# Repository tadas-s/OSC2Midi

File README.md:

# OSC2Midi

ESP8266 based OSC <-> Midi wireless bridge.

It is mostly meant to be used with [TouchOSC][1] but it will work with
any [OSC message source][2].

## Library dependencies

Project uses:
  * https://github.com/FortySevenEffects/arduino_midi_library/
  * https://github.com/CNMAT/OSC

## Hardware

Based on a generic ESP8266-12f board and the following guides to hook
up ESP8266 and do MIDI i/o:

  * [MIDI Input][4]
  * [MIDI Output][3]

Midi I/O uses [SoftwareSerial][5] mostly to allow debug logging via
primary serial port.

## Schematic

Note! Do checkout the KiCad project instead. Image below is for quick preview only.

## Flashing firmware

To flash the firmware I'm using FTDI cable with [flash+reset circuit][8].

## Hardware ideas / roadmap / TODO

  * Find a reasonable enclosure and adapt layout to it.
  * [MCP73833][7] based battery charging circuit + microusb input for power.
  * Maaaaybe i2c screen.

## OSC message formats

All messages are expected to have payload of 1 or 2 floats with range
from 0 to 127.

### /midi/cc/{cc} + 1 float

Will send control change message for `{cc}` number.

### /midi/cc/{ccA}/{ccB}/.../{index} + 1 float

Will send control change message for CC specified by `{index}`. For
example:

  * /midi/cc/10/12/15/1 -> CC to 10
  * /midi/cc/10/12/15/3 -> CC to 15

This is meant to be used with TouchOSC groups of faders. For example,
my [MicroKORG][6] preset includes a fader group of 4 to control
amp ADSR: `/midi/cc/73/75/70/72`

### /midi/cc/{ccA}/{ccB} + 2 floats

This sends two control change messages to `{ccA}` and `{ccB}`. This is
meant to be used with TouchOSC XY pads.

## Current prototype

Rather crude build, but it works:

## Hello people of the future

So it seems GitHub is about to take a snapshot of active open source repositories
and put it into cold storage that should last 1000 years. Hence this section:
a change for the sake of it. Exact criteria is not clear, but hope this
repository makes it to the archive.

[1]: http://hexler.net/software/touchosc
[2]: https://en.wikipedia.org/wiki/Open_Sound_Control
[3]: https://www.arduino.cc/en/Tutorial/Midi
[4]: http://libremusicproduction.com/tutorials/arduino-and-midi-in
[5]: https://www.arduino.cc/en/Reference/SoftwareSerial
[6]: http://www.korg.com/us/products/synthesizers/microkorg/
[7]: https://www.microchip.com/wwwproducts/en/en027785
[8]: https://github.com/tadas-s/esp8266-autoreset

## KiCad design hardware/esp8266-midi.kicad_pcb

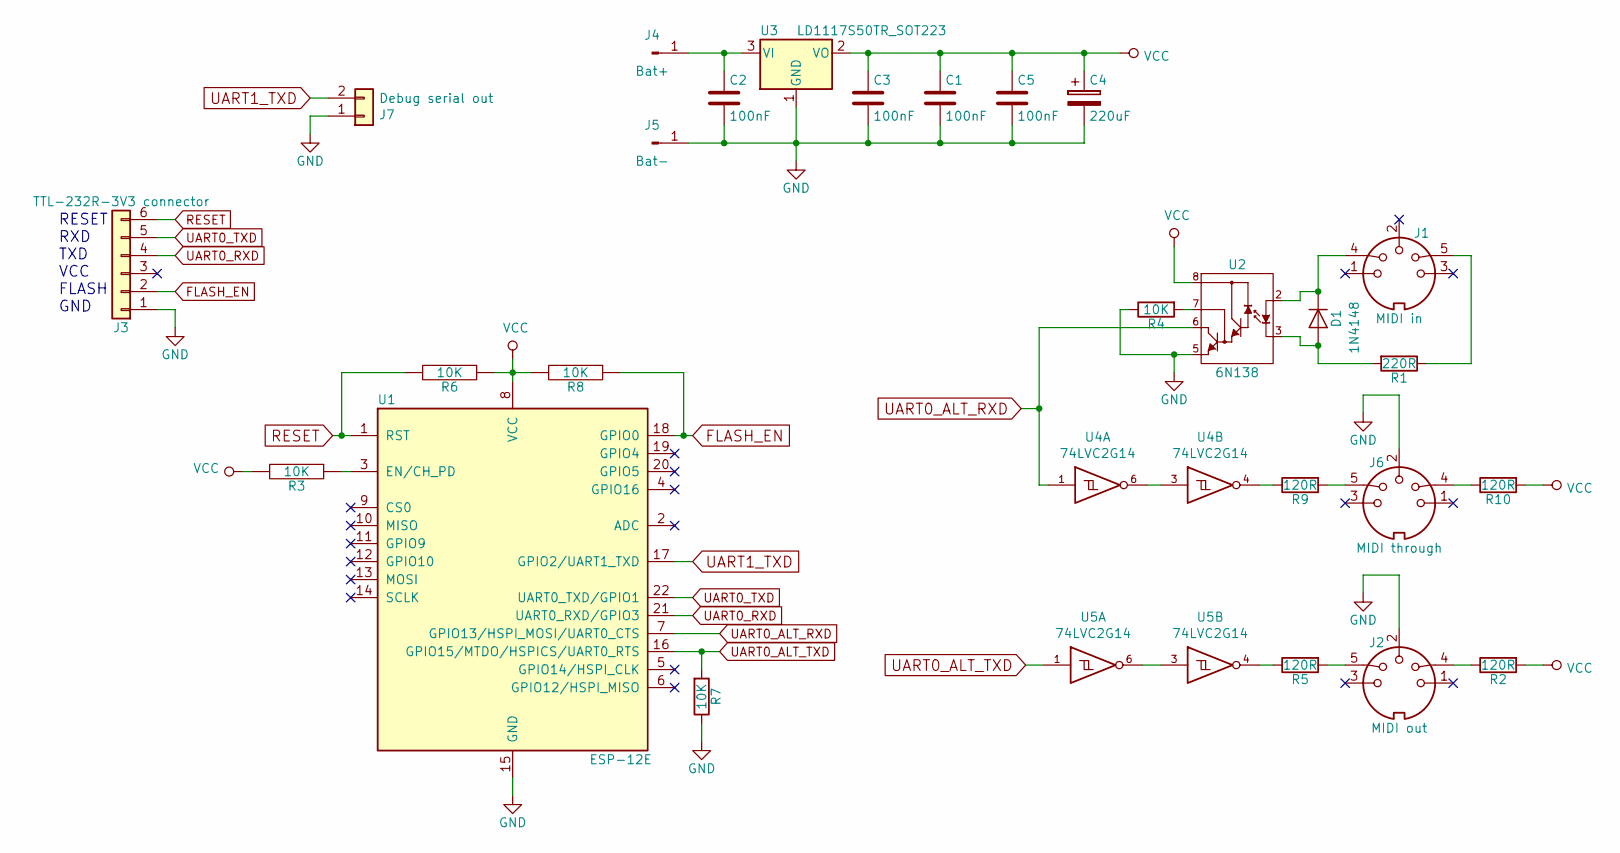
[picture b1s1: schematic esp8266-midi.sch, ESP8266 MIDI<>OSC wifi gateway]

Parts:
C1, C2, C3, C5: 100nF; C_0805_HandSoldering
C4: 220uF; CP_Elec_6.3x5.8
D1: 1N4148; D_SOD-323_HandSoldering
J1: MIDI in; SDS-50J
J2: MIDI out; SDS-50J
J3: TTL-232R-3V3 connector; Pin_Header_Straight_1x06_Pitch2.54mm
J4: Bat+; SolderWirePad_single_0-8mmDrill
J5: Bat-; SolderWirePad_single_0-8mmDrill
J6: MIDI through; SDS-50J
J7: Debug serial out; Pin_Header_Straight_1x02_Pitch2.54mm
R1: 220R; R_0805_HandSoldering
R2, R5, R9, R10: 120R; R_0805_HandSoldering
R3, R4, R6, R7, R8: 10K; R_0805_HandSoldering
U1: ESP-12E
U2: 6N138; DIP-8_W7.62mm_SMDSocket_SmallPads
U3: LD1117S50TR_SOT223; SOT-223
U4, U5: 74LVC2G14; SOT-23-6_Handsoldering

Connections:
FLASH_EN: J3.2, R8.1, U1.18 (GPIO0)
GND: C1.2, C2.2, C3.2, C4.2, C5.2, J2.2, J3.1, J5.1, J6.2, J7.1, R4.1, R7.1, U1.15 (GND), U2.5 (GND), U3.1 (GND), U4.2 (GND), U5.2 (GND)
unnamed: C2.1, J4.1, U3.3 (VI)
unnamed: D1.1 (K), J1.4, U2.2 (A)
unnamed: D1.2 (A), R1.2, U2.3 (K)
unnamed: J1.5, R1.1
unnamed: J2.4, R2.1
unnamed: J2.5, R5.2
unnamed: J6.4, R10.1
unnamed: J6.5, R9.2
unnamed: R3.1, U1.3 (EN/CH_PD)
unnamed: R4.2, U2.7 (Vb)
unnamed: R5.1, U5.4
unnamed: R9.1, U4.4
unnamed: U4.3, U4.6
unnamed: U5.3, U5.6
RESET: J3.6, R6.2, U1.1 (RST)
UART0_ALT_RXD: U1.7 (GPIO13/HSPI_MOSI/UART0_CTS), U2.6 (Vo), U4.1
UART0_ALT_TXD: R7.2, U1.16 (GPIO15/MTDO/HSPICS/UART0_RTS), U5.1
UART0_RXD: J3.4, U1.21 (UART0_RXD/GPIO3)
UART0_TXD: J3.5, U1.22 (UART0_TXD/GPIO1)
UART1_TXD: J7.2, U1.17 (GPIO2/UART1_TXD)
VCC: C1.1, C3.1, C4.1, C5.1, R2.2, R3.2, R6.1, R8.2, R10.2, U1.8 (VCC), U2.8 (Vcc), U3.2 (VO), U4.5 (VCC), U5.5 (VCC)

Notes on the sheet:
RESET RXD TXD VCC FLASH GND

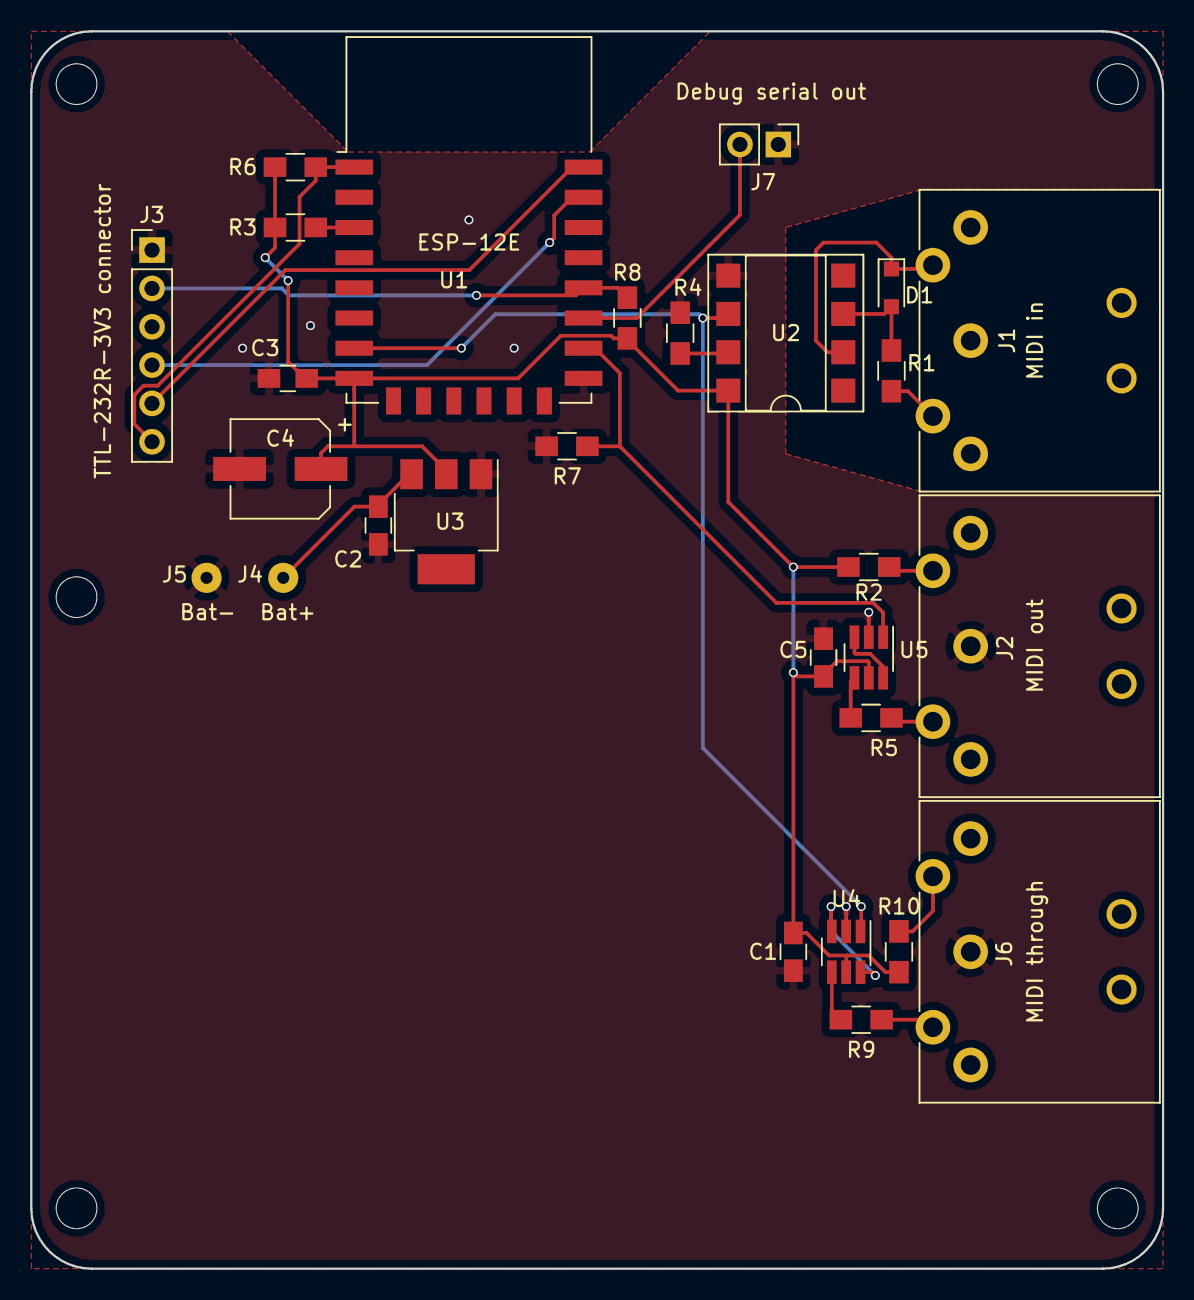
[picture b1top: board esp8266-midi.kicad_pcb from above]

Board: 2 copper layers, 75.0 x 82.0 mm, 28 parts (0 on the bottom side), 23 nets.

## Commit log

2016-08-15 Quick and dirty OSC<->Midi bridge mockup
2016-08-15 Add a note about library dependencies
2018-03-08 Misc: note about software serial pins
2018-03-08 Update README.md
    Mixed up links to midi in and out schematics
2018-03-10 Initial rev of schematic and PCB, WIP
2018-03-10 Misc README.md updates
2018-03-13 Misc README.md notes
2018-04-03 Misc: tweaks trying to figure out Android's "authentication error"
    Maybe it's the early start, maybe something else.. Or maybe persisted
    credentials from before?
2018-04-04 Update schematic: now uses ESP-12E footprint from standard KiCad lib
    + Misc silly fixes.
2018-04-04 Updated PCB using correct ESP-12E footprint
2018-04-08 Soft serial requires pins to be configured before starting
    Also, due to the way hardware works it input must always be pulled
    high.
2018-04-08 Don't use the same port to send controls over back to the controller
2018-04-08 Schematic change: do not pull up opto-isolator output + change output resistor loop values
    1. Pull up can be done by the micro itself.
    2. 220 ohm examples are taken from Midi spec when voltage is 5v. To match the
    the same current when using 3.3v micro resistors were reduced to 120ohm.
2018-04-08 Hopefully fixed layout now
2018-04-09 Before resizing the board a bit
2018-04-09 Small resize of the board + relocating some stuff + some rounded ground zone corners
2018-04-11 Notes added by 'git notes add'
2018-04-24 Misc cleanup: remove some TODOs/notes. Schematic is verified / works.
2018-04-24 Not sure why but KiCad decided to update project file a bit...
2018-04-24 Add schematic preview to README.md
2018-04-24 Slightly better debug info: display midi cc+values instead of just message only
2018-05-29 Misc: re-freshed schematic preview
2018-06-02 Misc: change "candidate" enclosure to CRDCGG003 by CamdenBoss
2018-06-02 Misc: ditch the reset/flash minimum circuit diagram example
    Will be using external programming adapter with dtrset reset method.
2018-06-02 Change schematic to use external flash enable + reset circuit
    Less components + all those switches are expensive and cumbersome to use ;)
    And another misc change: remove a probs redundant power supply smoothing
    capacitor.
2018-06-02 Assign SMD footprints to (almost) all components
2018-06-03 New layout with (mostly) smd components, pcb shaped for CRDCGG003 enclosure
2018-06-24 Misc: new notes on programming
2018-06-24 Pics of first crude prototype in enclosure
2018-07-09 Misc: remove a misleading / out of date code comment
2018-10-28 Glide: dirty dirty wip
2018-11-03 Moving to vscode+platformio: move the main source file
2018-11-03 Moving to vscode+platformio: vscode/pio specific gitignores
2018-11-03 Moving to vscode+platformio: rest of pio specific project stuff
2018-11-03 Set upload_resetmethod to ck
    Since I'm using a fancy programmer with auto-reset feature.
2018-11-03 For faster uploads: change speed + limit used flash to 512k
    Details: https://docs.platformio.org/en/latest/platforms/espressif8266.html
2018-11-10 Serial monitor: set speed + rts flag
    RTS pulled low is required so openning serial monitor does not reset the board
    in firmware flash mode.
2018-11-13 Misc: trim trailing whitespace setting
2018-11-13 Glide: move update function to the ControlChangeState class itself
2018-11-13 Glide: do not make unnecessary midi cc messages when moving towards the target value
2018-11-24 Kicad5: schematic after converting to kicad5, no other changes
2018-11-24 Kicad5: netlist after converting to kicad5
2018-11-24 Kicad5: pcb after converting to kicad5
2018-12-05 Unit tests: add native platform env for some plain C code tests
2018-12-05 Misc: vscode settings update.. whatever it means.
2018-12-05 Unit tests: rename main .ino file to .cpp, move stuff to be tested to a local lib
    This also switches from Arudino String class to standard c strings.
2018-12-05 Unit tests: actual test cases for getCC!
2018-12-07 Misc: add MIT license ... ¯\_(ツ)_/¯
2018-12-08 Project debug.h include with DEBUG_MSG macro
    To be enabled by defining DEBUG_ESP_PORT via build flags.
2018-12-08 Rewrite debug statements to use DEBUG_MSG + some other misc changes
    Other miscalenous stuff:
    * Blink the built-in led to show activity
    * Ignore packets larger than buffer
2018-12-08 Schematic changes: midi through, midi via hardware serial, debug serial out
2018-12-08 Misc: swap debug output pins
2018-12-08 Updated PCB with new components .. little questionable / not final.
2018-12-08 New pcb: with midi through, all 3 connectors are now on the side
    PCB will be mount flipped on top of enclosure. In future it will allow having
    pcb mount push buttons + display available on front of enclosure.
2018-12-08 Misc: add exact box manufacturer drawing
2018-12-09 Misc: add some extra labels to have little more meaningful net names
2018-12-09 Misc: fix some 3d shape paths after upgrade to kicad5
2018-12-15 Use uart0 for midi and uart1 for debug messages
    This ditches SoftwareSerial for which I suspect was causing crashes.
    This also ditches led blinking since built-in esp12e led is on the same pin as
    uart1 tx.
2018-12-15 Macro to dump (almost) full OSC message details to the debug out
2019-01-05 Use alternative uart0 pins for midi i/o
    uart0 pushes bunch of rubbish messages on boot up. This means some pretty random
    messages on the midi out port. To fix this midi i/o uses alternative uart0 pins
    which can be enabled after microcontroller is booted by calling 'Serial.swap()'.
    Alternative TX pin needs to be pulled down during boot, but a connected midi
    instrument pull it up. Therefore the buffering using the same dual nand
    (74LVC2G14) as for the midi through port.
2019-01-06 Misc: rename main file to main.cpp
2019-02-01 Kicad5 update woes again: eeschema rescues
2019-02-01 Kicad5 update woes again: netlist update
2019-02-01 Misc: fix ESP-12E 3d model path
2019-02-01 Update README.md: schematic image
2019-02-01 Project file bump
2020-01-30 Misc: "hello people of the future"
    Just trying to get this repository into cold storage ;) .. Please ignore.
